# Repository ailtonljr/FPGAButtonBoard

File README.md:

# FPGAButtonBoard - Placa de entrada para o DE0-Nano

TODO: Adicionar a pinagem

Observações:

DIP switches estão invertidos.
Botões não estão invertidos.

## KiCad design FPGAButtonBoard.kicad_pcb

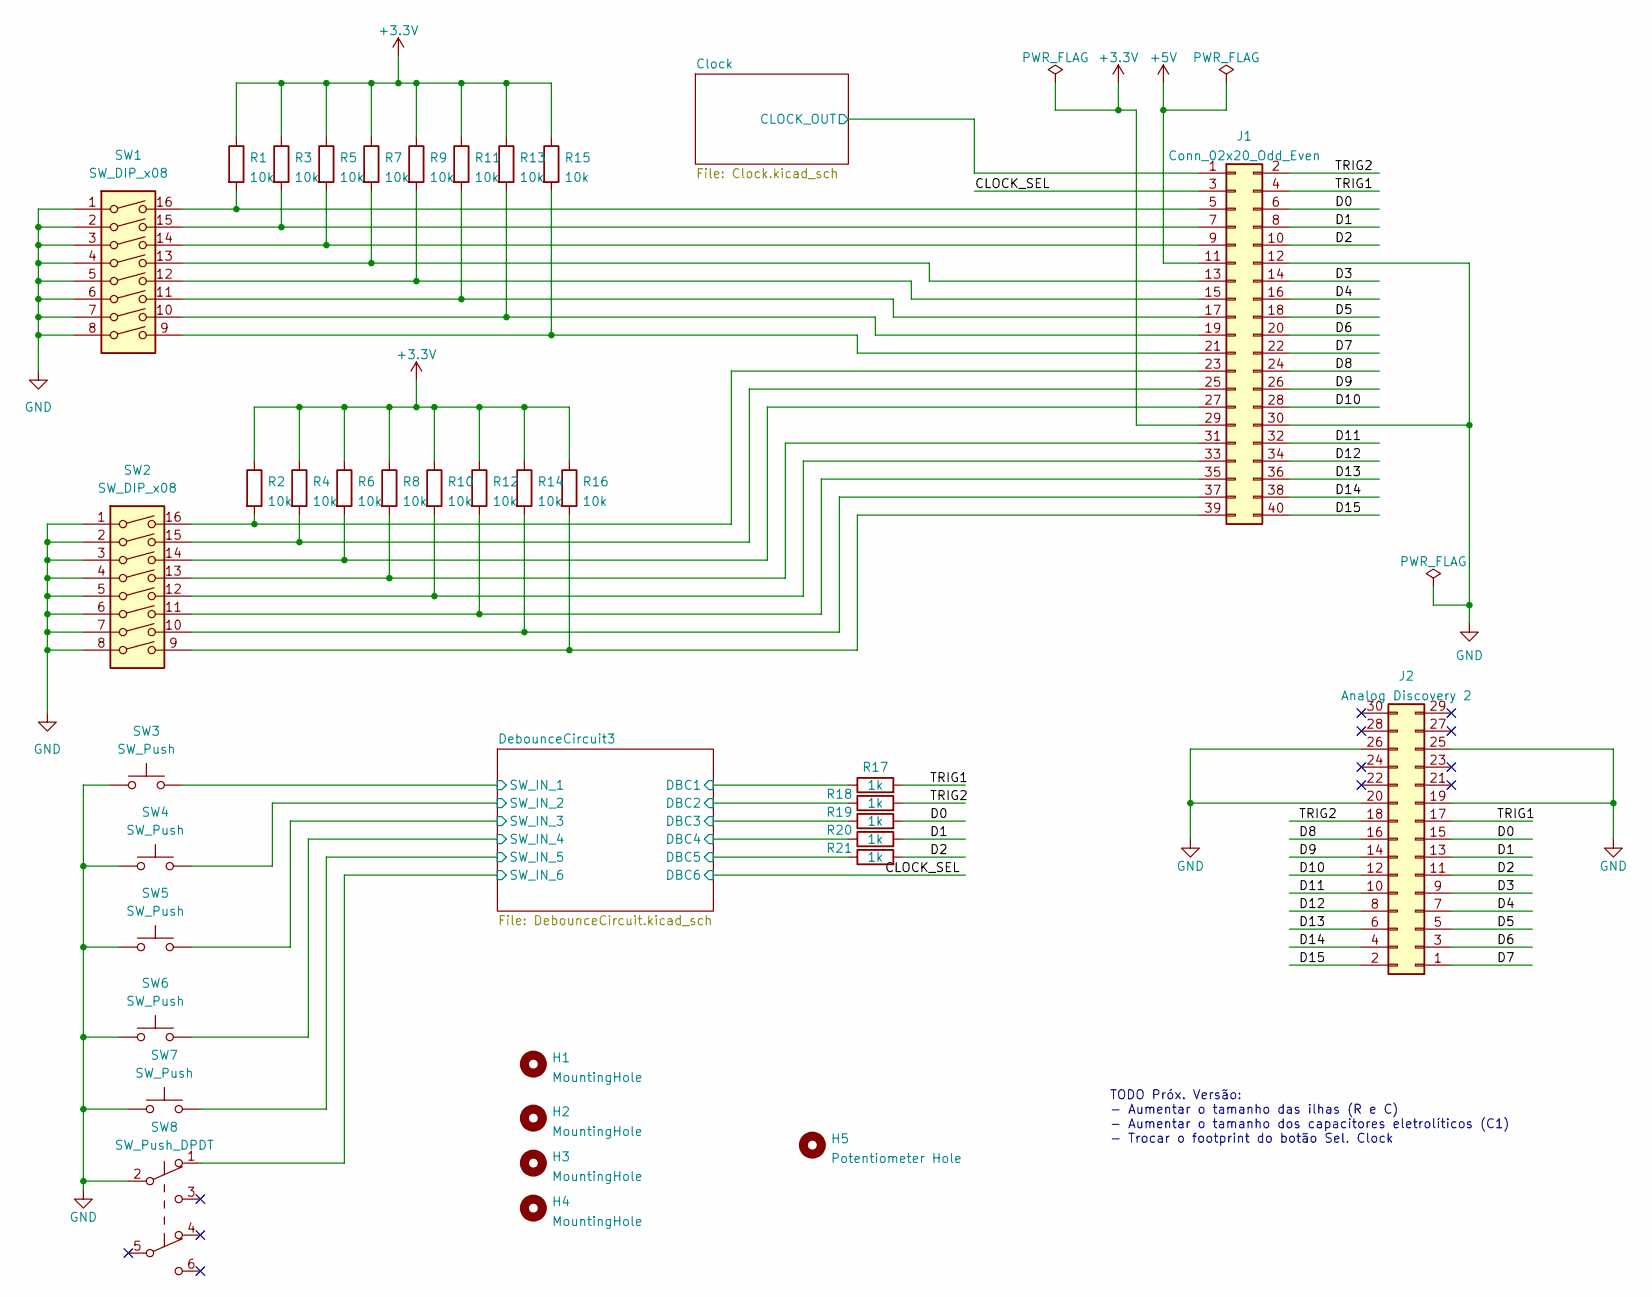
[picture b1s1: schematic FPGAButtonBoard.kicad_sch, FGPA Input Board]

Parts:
H1, H2, H3, H4: MountingHole; MountingHole_3.2mm_M3
H5: Potentiometer Hole; MountingHole_8.4mm_M8
J1: Conn_02x20_Odd_Even; PinSocket_2x20_P2.54mm_Vertical
J2: Analog Discovery 2; IDC-Header_2x15_P2.54mm_Vertical
R1, R2, R3, R4, R5, R6, R7, R8, R9, R10, R11, R12, R13, R14, R15, R16: 10k; R_Axial_DIN0207_L6.3mm_D2.5mm_P7.62mm_Horizontal
R17, R18, R19, R20, R21: 1k; R_Axial_DIN0207_L6.3mm_D2.5mm_P7.62mm_Horizontal
SW1, SW2: SW_DIP_x08; SW_DIP_SPSTx08_Slide_6.7x21.88mm_W7.62mm_P2.54mm_LowProfile
SW3, SW4, SW5, SW6, SW7: SW_Push; SW_PUSH_6mm
SW8: SW_Push_DPDT; Nidec_Copal_SH-7010C_Mod

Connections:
+3V3: J1.29, R1.1, R2.1, R3.1, R4.1, R5.1, R6.1, R7.1, R8.1, R9.1, R10.1, R11.1, R12.1, R13.1, R14.1, R15.1, R16.1; also elsewhere on the board
+5V: J1.11; also elsewhere on the board
/CLOCK_SEL: J1.3; also elsewhere on the board
/Clock/CLOCK_OUT: J1.1; also elsewhere on the board
/D0: J1.6, J2.15, R19.2
/D1: J1.8, J2.13, R20.2
/D2: J1.10, J2.11, R21.2
/D3: J1.14, J2.9
/D4: J1.16, J2.7
/D5: J1.18, J2.5
/D6: J1.20, J2.3
/D7: J1.22, J2.1
/D8: J1.24, J2.16
/D9: J1.26, J2.14
/D10: J1.28, J2.12
/D11: J1.32, J2.10
/D12: J1.34, J2.8
/D13: J1.36, J2.6
/D14: J1.38, J2.4
/D15: J1.40, J2.2
/DebounceCircuit3/DBC1: R17.1; also elsewhere on the board
/DebounceCircuit3/DBC2: R18.1; also elsewhere on the board
/DebounceCircuit3/DBC3: R19.1; also elsewhere on the board
/DebounceCircuit3/DBC4: R20.1; also elsewhere on the board
/DebounceCircuit3/DBC5: R21.1; also elsewhere on the board
/DebounceCircuit3/SW_IN_1: SW3.2; also elsewhere on the board
/DebounceCircuit3/SW_IN_2: SW4.2; also elsewhere on the board
/DebounceCircuit3/SW_IN_3: SW5.2; also elsewhere on the board
/DebounceCircuit3/SW_IN_4: SW6.2; also elsewhere on the board
/DebounceCircuit3/SW_IN_5: SW7.2; also elsewhere on the board
/DebounceCircuit3/SW_IN_6: SW8.1 (A); also elsewhere on the board
/TRIG1: J1.4, J2.17, R17.2
/TRIG2: J1.2, J2.18, R18.2
GND: J1.12, J1.30, J2.19, J2.20, J2.25, J2.26, SW1.1, SW1.2, SW1.3, SW1.4, SW1.5, SW1.6, SW1.7, SW1.8, SW2.1, SW2.2, SW2.3, SW2.4, SW2.5, SW2.6, SW2.7, SW2.8, SW3.1, SW4.1, SW5.1, SW6.1, SW7.1, SW8.2 (B); also elsewhere on the board
unnamed: J1.5, R1.2, SW1.16
unnamed: J1.7, R3.2, SW1.15
unnamed: J1.9, R5.2, SW1.14
unnamed: J1.13, R7.2, SW1.13
unnamed: J1.15, R9.2, SW1.12
unnamed: J1.17, R11.2, SW1.11
unnamed: J1.19, R13.2, SW1.10
unnamed: J1.21, R15.2, SW1.9
unnamed: J1.23, R2.2, SW2.16
unnamed: J1.25, R4.2, SW2.15
unnamed: J1.27, R6.2, SW2.14
unnamed: J1.31, R8.2, SW2.13
unnamed: J1.33, R10.2, SW2.12
unnamed: J1.35, R12.2, SW2.11
unnamed: J1.37, R14.2, SW2.10
unnamed: J1.39, R16.2, SW2.9

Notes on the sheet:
TODO Próx. Versão: - Aumentar o tamanho das ilhas (R e C) - Aumentar o tamanho dos capacitores eletrolíticos (C1) - Trocar o footprint do botão Sel. Clock

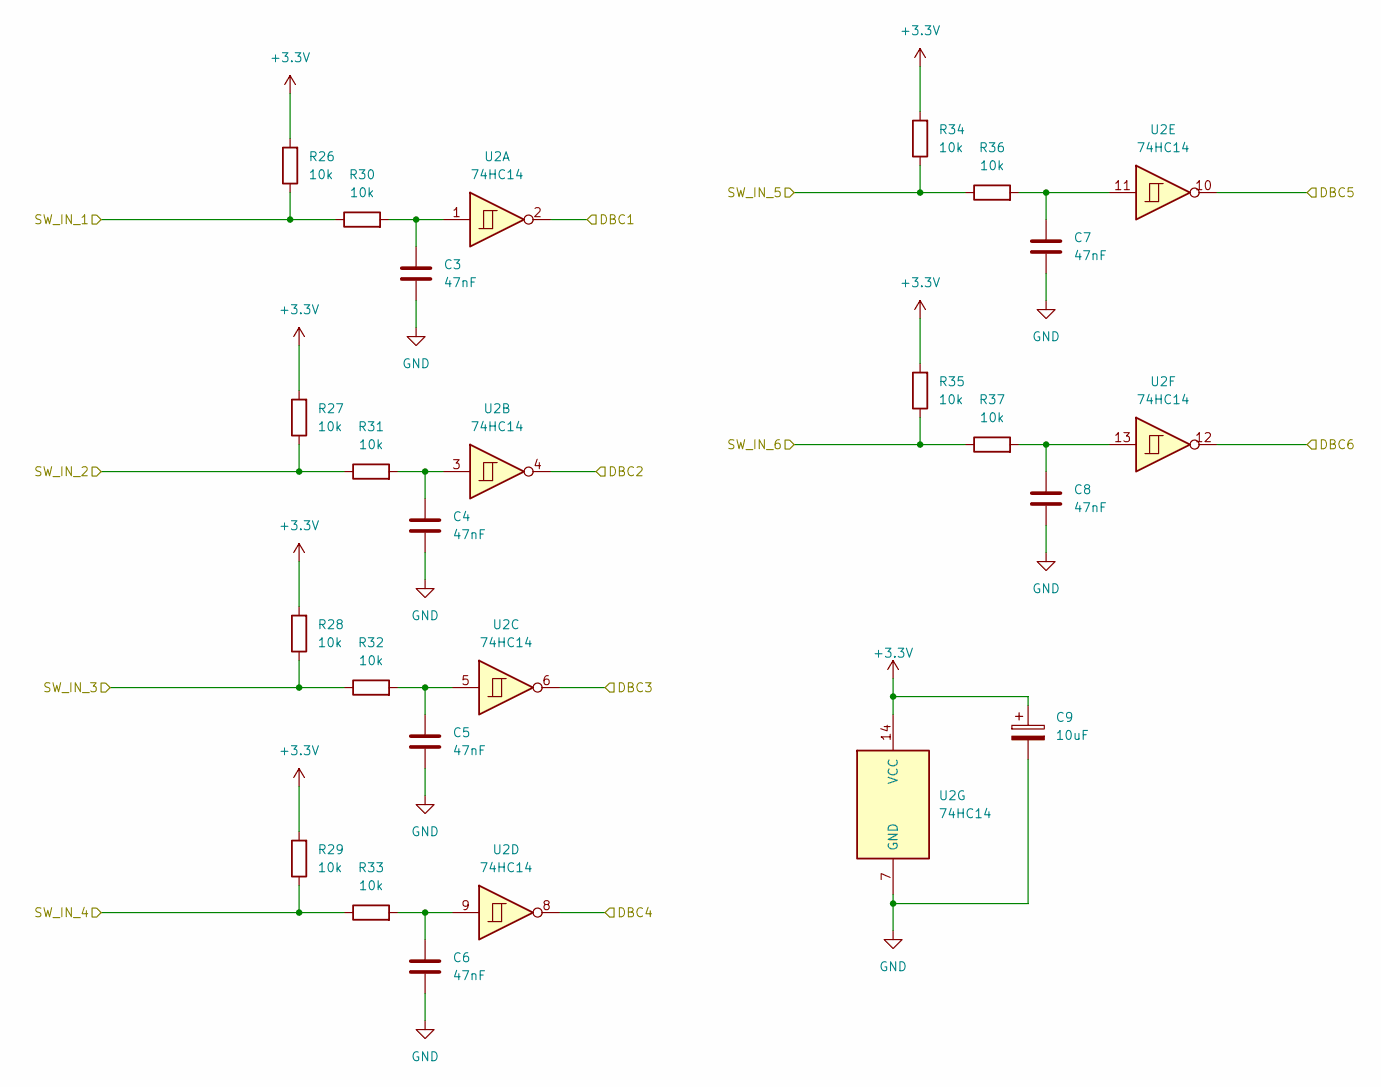
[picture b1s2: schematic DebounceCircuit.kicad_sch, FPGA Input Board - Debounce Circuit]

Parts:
C3, C4, C5, C6, C7, C8: 47nF; C_Rect_L7.0mm_W3.5mm_P5.00mm
C9: 10uF; CP_Radial_D4.0mm_P2.00mm
R26, R27, R28, R29, R30, R31, R32, R33, R34, R35, R36, R37: 10k; R_Axial_DIN0207_L6.3mm_D2.5mm_P7.62mm_Horizontal
U2: 74HC14; DIP-14_W7.62mm_Socket

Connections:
+3V3: C9.1, R26.2, R27.2, R28.2, R29.2, R34.2, R35.2, U2.14 (VCC); also elsewhere on the board
/CLOCK_SEL: U2.12; also elsewhere on the board
/DebounceCircuit3/DBC1: U2.2; also elsewhere on the board
/DebounceCircuit3/DBC2: U2.4; also elsewhere on the board
/DebounceCircuit3/DBC3: U2.6; also elsewhere on the board
/DebounceCircuit3/DBC4: U2.8; also elsewhere on the board
/DebounceCircuit3/DBC5: U2.10; also elsewhere on the board
/DebounceCircuit3/SW_IN_1: R26.1, R30.1; also elsewhere on the board
/DebounceCircuit3/SW_IN_2: R27.1, R31.1; also elsewhere on the board
/DebounceCircuit3/SW_IN_3: R28.1, R32.1; also elsewhere on the board
/DebounceCircuit3/SW_IN_4: R29.1, R33.1; also elsewhere on the board
/DebounceCircuit3/SW_IN_5: R34.1, R36.1; also elsewhere on the board
/DebounceCircuit3/SW_IN_6: R35.1, R37.1; also elsewhere on the board
GND: C3.2, C4.2, C5.2, C6.2, C7.2, C8.2, C9.2, U2.7 (GND); also elsewhere on the board
unnamed: C3.1, R30.2, U2.1
unnamed: C4.1, R31.2, U2.3
unnamed: C5.1, R32.2, U2.5
unnamed: C6.1, R33.2, U2.9
unnamed: C7.1, R36.2, U2.11
unnamed: C8.1, R37.2, U2.13

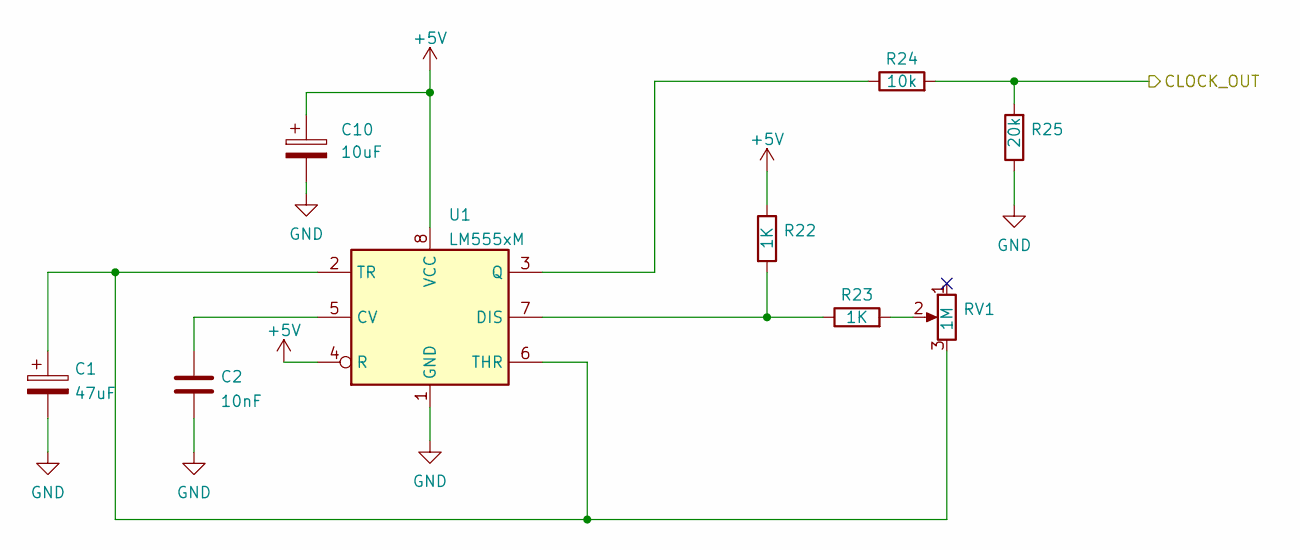
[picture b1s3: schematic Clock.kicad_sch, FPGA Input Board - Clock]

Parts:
C1: 47uF; CP_Radial_D4.0mm_P2.00mm
C2: 10nF; C_Rect_L7.0mm_W3.5mm_P5.00mm
C10: 10uF; CP_Radial_D4.0mm_P2.00mm
R22, R23: 1K; R_Axial_DIN0207_L6.3mm_D2.5mm_P7.62mm_Horizontal
R24: 10k; R_Axial_DIN0207_L6.3mm_D2.5mm_P7.62mm_Horizontal
R25: 20k; R_Axial_DIN0207_L6.3mm_D2.5mm_P7.62mm_Horizontal
RV1: 1M; Potentiometer_Alps_RK163_Single_Horizontal
U1: LM555xM; DIP-8_W7.62mm_Socket

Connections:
+5V: C10.1, R22.1, U1.4 (R), U1.8 (VCC); also elsewhere on the board
/Clock/CLOCK_OUT: R24.2, R25.2; also elsewhere on the board
GND: C1.2, C2.2, C10.2, R25.1, U1.1 (GND); also elsewhere on the board
unnamed: C1.1, RV1.3, U1.2 (TR), U1.6 (THR)
unnamed: C2.1, U1.5 (CV)
unnamed: R22.2, R23.1, U1.7 (DIS)
unnamed: R23.2, RV1.2
unnamed: R24.1, U1.3 (Q)

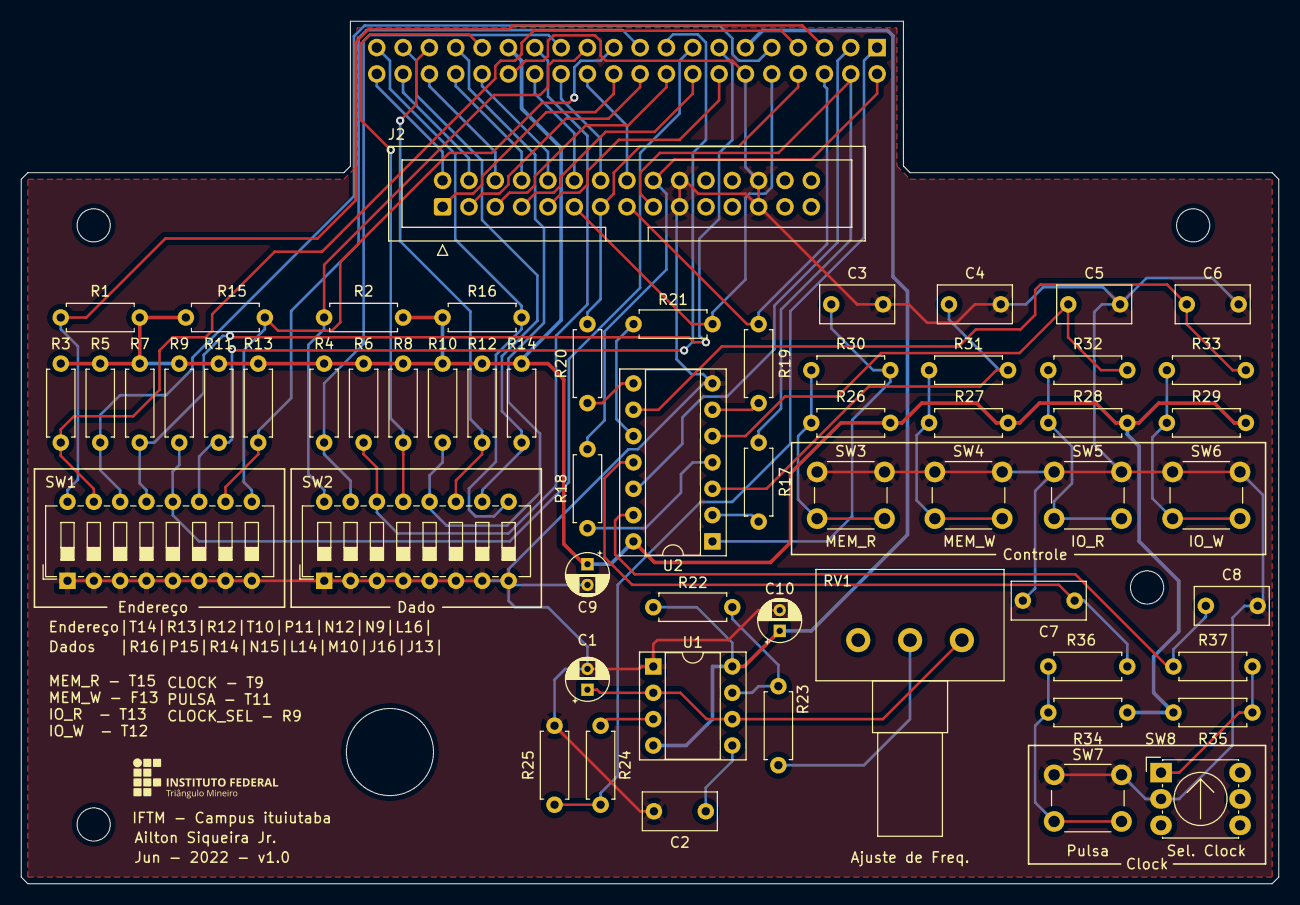
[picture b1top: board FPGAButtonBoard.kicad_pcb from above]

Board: 2 copper layers, 121.3 x 83.2 mm, 65 parts (1 on the bottom side), 61 nets.

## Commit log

2022-02-05 Primeiro commit
2022-05-12 Adicionado o circuito de Debounce.
2022-05-12 Adicionado os botões e clock. Adicionada interface com o Analog Discovery 2.
2022-06-01 Removido o circuito debounce do dipswitch
2022-06-01 Adicionado os furos de montagem. Definidos os footprints
2022-06-02 Organizado os componentes na placa.
2022-06-02 Definida a borda da placa.
2022-06-03 Corrigido o footprint dos capacitores. Adicionado um capacitor de bypass. Adicionado o ground plane e logo.
2022-06-03 Adicionados indicações dos elementos no silkscreen
2022-06-08 Adicionadas anotações dos pinos na placa.
2022-06-24 Corrigido o botão de seleção de Clock e valores dos capacitores.
2022-08-03 Atualizado os valores dos capacitores
2022-08-31 Corrigido um erro no silkscren. Opino do MEM_R está invertido com o MEM_W
